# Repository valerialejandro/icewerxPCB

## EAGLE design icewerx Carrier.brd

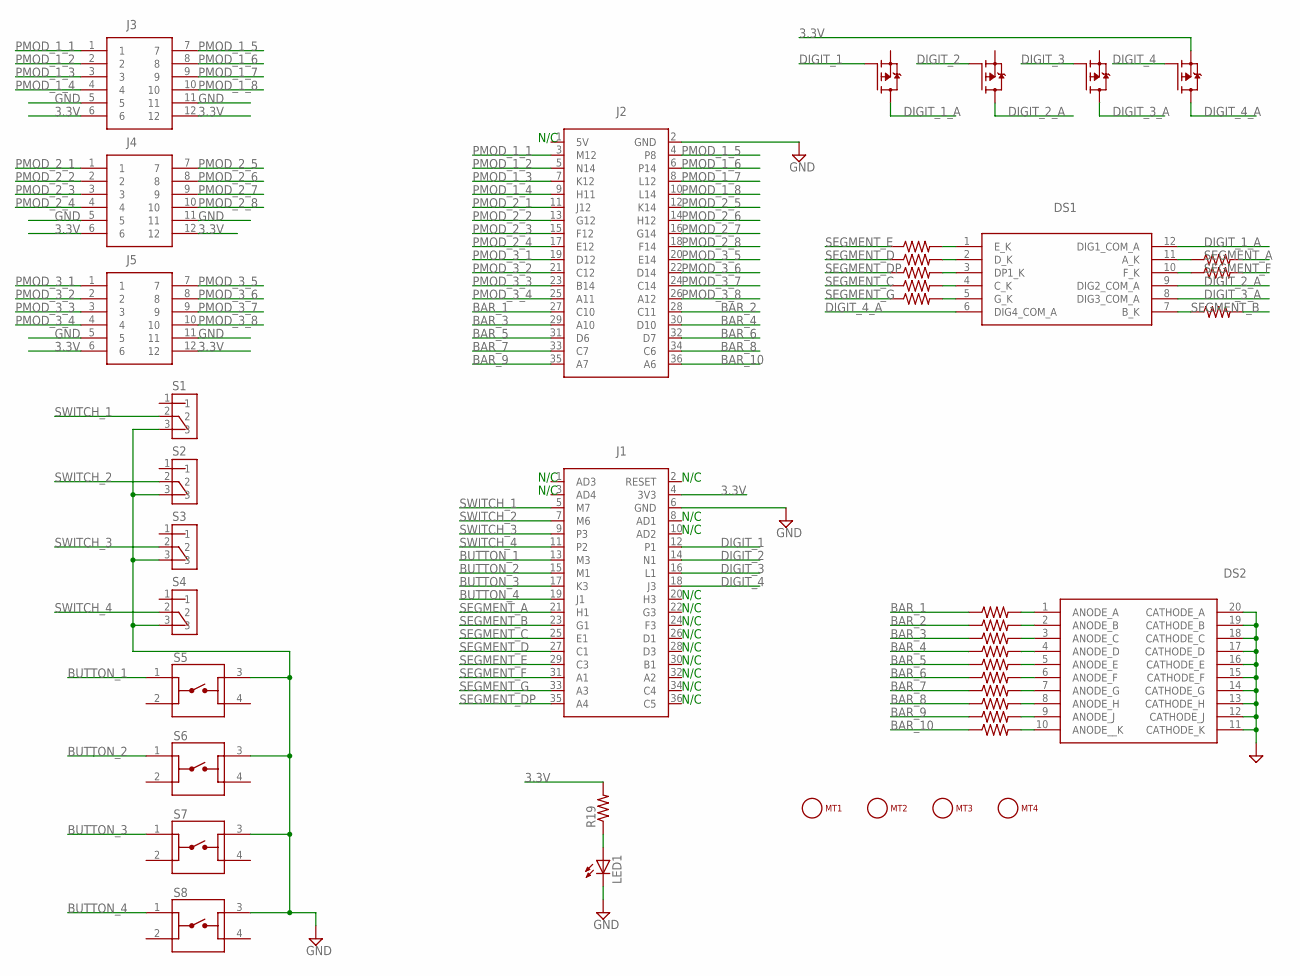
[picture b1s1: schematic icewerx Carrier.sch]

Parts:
DS1: LDQ-M282RI; LDQM282RI
DS2: LTA-1000G; DIPS762W50P254L2527H825Q20N
J1: ICEWERX-PL2; TE_4-1734506-1
J2: ICEWERX-PL3; TE_4-1734506-1
J3, J4, J5: PMOD-SOCKET-FOR-HOST-BOARD
LED1: LED5MM
MT1, MT2, MT3, MT4: MOUNTING_HOLE-125_250_ROUND; MT_125_250
Q1, Q2, Q3, Q4: NX2301P; SOT95P230X110-3N
R1, R2, R3, R4, R5, R6, R7, R8, R9, R10, R11, R12, R13, R14, R15, R16, R17, R18, R19: R-US_0204/5; 0204/5
S1, S2, S3, S4: OS102011MS2QN1; SW_OS102011MS2QN1
S5, S6, S7, S8: 1825910-7; SW_1825910-7

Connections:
3.3V: J1.4 (3V3), J3.6, J3.12, J4.6, J4.12, J5.6, J5.12, Q4.2 (S), R19.2
BAR_1: J2.27 (C10), R1.1
BAR_2: J2.28 (C11), R2.1
BAR_3: J2.29 (A10), R3.1
BAR_4: J2.30 (D10), R5.1
BAR_5: J2.31 (D6), R4.1
BAR_6: J2.32 (D7), R6.1
BAR_7: J2.33 (C7), R7.1
BAR_8: J2.34 (C6), R8.1
BAR_9: J2.35 (A7), R10.1
BAR_10: J2.36 (A6), R9.1
BUTTON_1: J1.13 (M3), S5.1
BUTTON_2: J1.15 (M1), S6.1
BUTTON_3: J1.17 (K3), S7.1
BUTTON_4: J1.19 (J1), S8.1
DIGIT_1: J1.12 (P1), Q1.1 (G)
DIGIT_1_A: DS1.12 (DIG1_COM_A), Q1.3 (D)
DIGIT_2: J1.14 (N1), Q2.1 (G)
DIGIT_2_A: DS1.9 (DIG2_COM_A), Q2.3 (D)
DIGIT_3: J1.16 (L1), Q3.1 (G)
DIGIT_3_A: DS1.8 (DIG3_COM_A), Q3.3 (D)
DIGIT_4: J1.18 (J3), Q4.1 (G)
DIGIT_4_A: DS1.6 (DIG4_COM_A), Q4.3 (D)
GND: DS2.11 (CATHODE_K), DS2.12 (CATHODE_J), DS2.13 (CATHODE_H), DS2.14 (CATHODE_G), DS2.15 (CATHODE_F), DS2.16 (CATHODE_E), DS2.17 (CATHODE_D), DS2.18 (CATHODE_C), DS2.19 (CATHODE_B), DS2.20 (CATHODE_A), J1.6 (GND), J2.2 (GND), J3.5, J3.11, J4.5, J4.11, J5.5, J5.11, LED1.K (C), S1.3, S2.3, S3.3, S4.3, S5.3, S6.3, S7.3, S8.3
unnamed: DS1.1 (E_K), R11.2
unnamed: DS1.2 (D_K), R12.2
unnamed: DS1.3 (DP1_K), R13.2
unnamed: DS1.4 (C_K), R14.2
unnamed: DS1.5 (G_K), R15.2
unnamed: DS1.11 (A_K), R16.1
unnamed: DS1.7 (B_K), R18.1
unnamed: DS2.1 (ANODE_A), R1.2
unnamed: DS2.2 (ANODE_B), R2.2
unnamed: DS2.3 (ANODE_C), R3.2
unnamed: DS2.5 (ANODE_E), R4.2
unnamed: DS2.4 (ANODE_D), R5.2
unnamed: DS2.6 (ANODE_F), R6.2
unnamed: DS2.8 (ANODE_H), R8.2
unnamed: DS2.10 (ANODE__K), R9.2
unnamed: DS2.9 (ANODE_J), R10.2
unnamed: DS2.7 (ANODE_G), R7.2
unnamed: LED1.A, R19.1
unnamed: DS1.10 (F_K), R17.1
PMOD_1_1: J2.3 (M12), J3.1
PMOD_1_2: J2.5 (N14), J3.2
PMOD_1_3: J2.7 (K12), J3.3
PMOD_1_4: J2.9 (H11), J3.4
PMOD_1_5: J2.4 (P8), J3.7
PMOD_1_6: J2.6 (P14), J3.8
PMOD_1_7: J2.8 (L12), J3.9
PMOD_1_8: J2.10 (L14), J3.10
PMOD_2_1: J2.11 (J12), J4.1
PMOD_2_2: J2.13 (G12), J4.2
PMOD_2_3: J2.15 (F12), J4.3
PMOD_2_4: J2.17 (E12), J4.4
PMOD_2_5: J2.12 (K14), J4.7
PMOD_2_6: J2.14 (H12), J4.8
PMOD_2_7: J2.16 (G14), J4.9
PMOD_2_8: J2.18 (F14), J4.10
PMOD_3_1: J2.19 (D12), J5.1
PMOD_3_2: J2.21 (C12), J5.2
PMOD_3_3: J2.23 (B14), J5.3
PMOD_3_4: J2.25 (A11), J5.4
PMOD_3_5: J2.20 (E14), J5.7
PMOD_3_6: J2.22 (D14), J5.8
PMOD_3_7: J2.24 (C14), J5.9
PMOD_3_8: J2.26 (A12), J5.10
SEGMENT_A: J1.21 (H1), R16.2
SEGMENT_B: J1.23 (G1), R18.2
SEGMENT_C: J1.25 (E1), R14.1
SEGMENT_D: J1.27 (C1), R12.1
SEGMENT_DP: J1.35 (A4), R13.1
SEGMENT_E: J1.29 (C3), R11.1
SEGMENT_F: J1.31 (A1), R17.2
SEGMENT_G: J1.33 (A3), R15.1
SWITCH_1: J1.5 (M7), S1.2
SWITCH_2: J1.7 (M6), S2.2
SWITCH_3: J1.9 (P3), S3.2
SWITCH_4: J1.11 (P2), S4.2

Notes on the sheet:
N/C

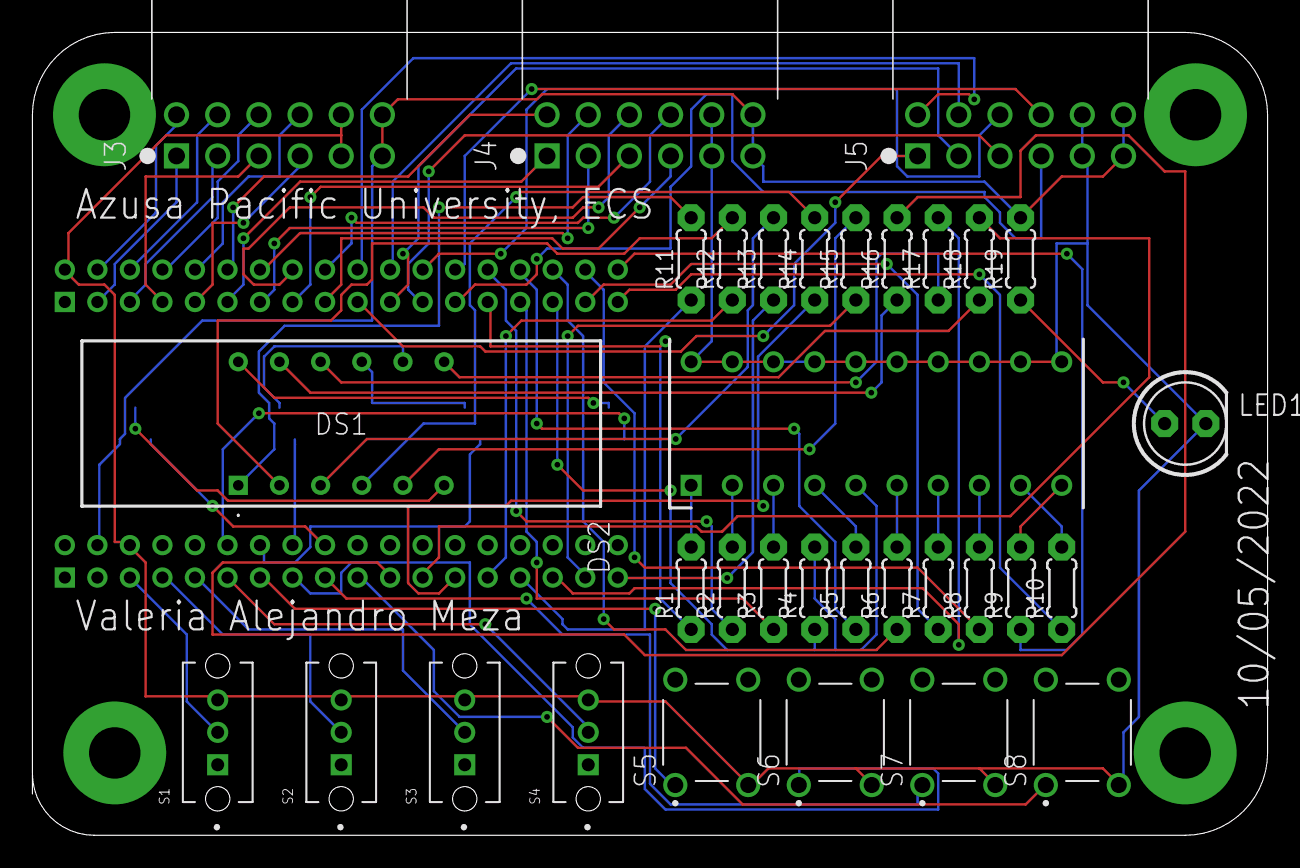
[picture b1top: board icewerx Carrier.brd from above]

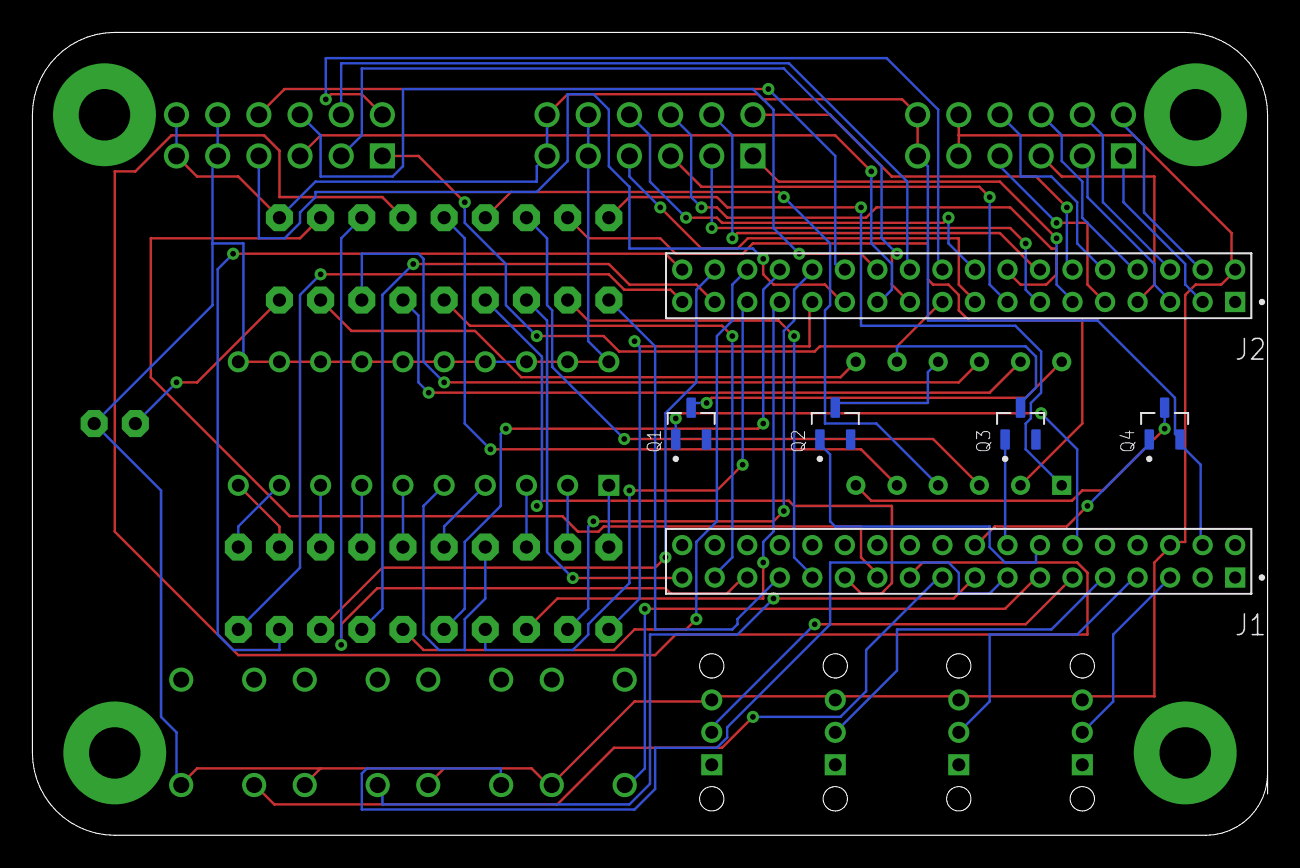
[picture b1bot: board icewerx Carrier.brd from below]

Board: 2 copper layers, 76.2 x 49.5 mm, 43 parts (6 on the bottom side), 79 nets.
